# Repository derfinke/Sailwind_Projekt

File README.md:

# Projektarbeit: Sailwind Steuerung
 \
Firmware/Schaltplan für die Steuerung des Sailwind 4.0 Projekts.\
[ Für weitere Informationen](https://www.sailwind-power.eu/)

## Geteilte Dokumente
[Bauteile Tabelle](https://drive.google.com/drive/folders/1qaNF0T8h1C8PEslQvWO4vngNG08Ppogr?usp=share_link)

## Roadmap
- [x] Erstellung des Schaltplans
- [ ] Erstellung des PCB Designs
	- [x] Auswahl der Bauteile
- [ ] Erstellung der Firmware
	- [x] Definieren der genutzen Ports
	- [ ] Definition des Ethernet Protokoll
	- [ ] Siehe [open issues](https://github.com/derfinke/Sailwind_Projekt/issues)

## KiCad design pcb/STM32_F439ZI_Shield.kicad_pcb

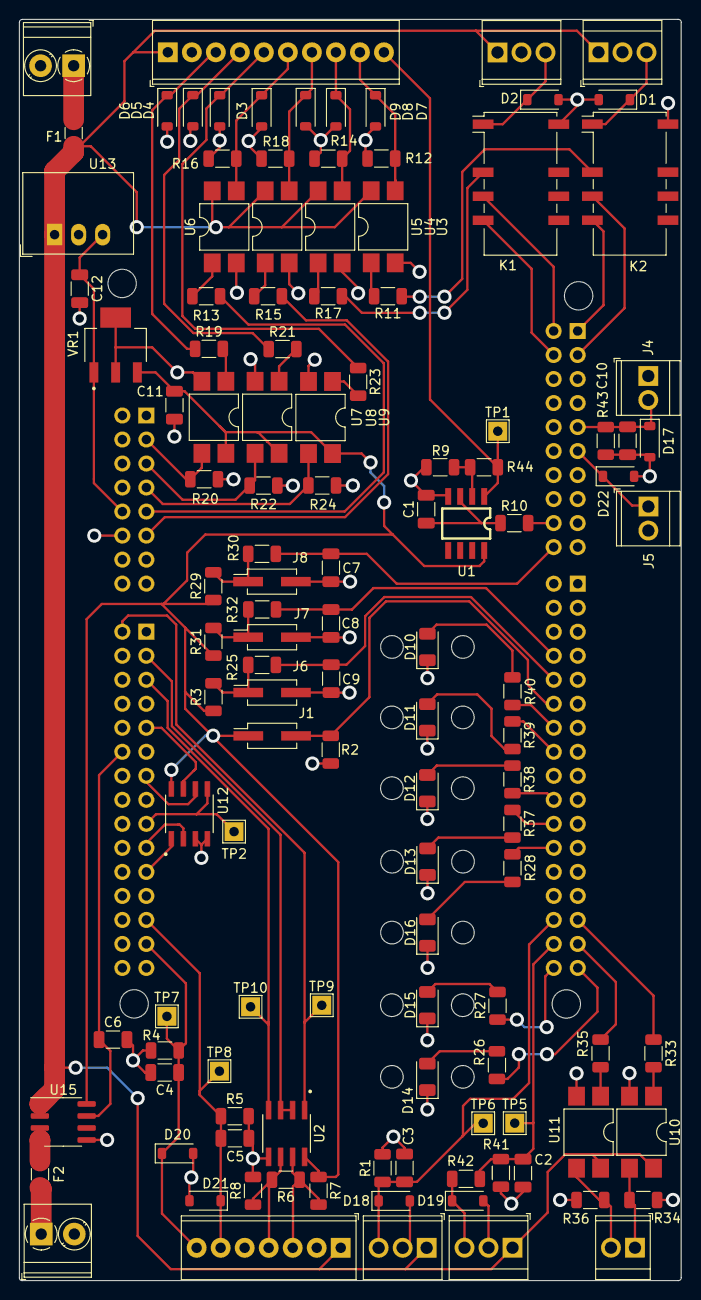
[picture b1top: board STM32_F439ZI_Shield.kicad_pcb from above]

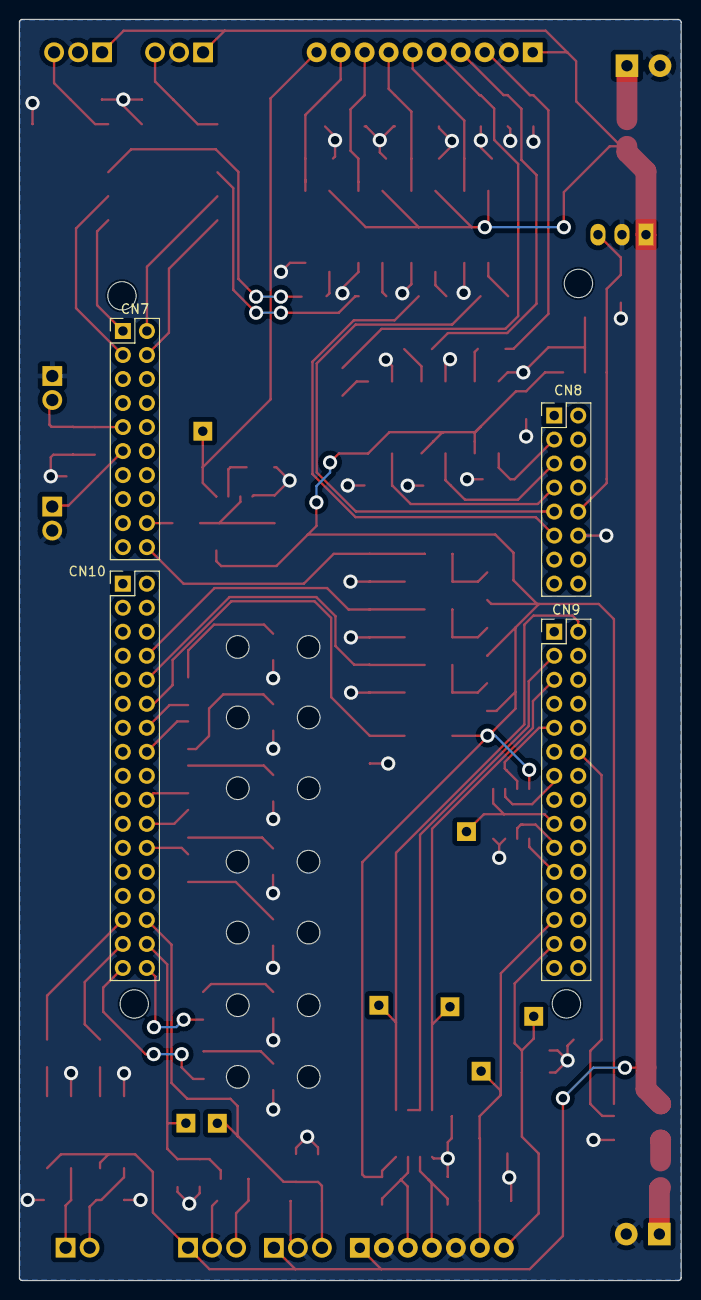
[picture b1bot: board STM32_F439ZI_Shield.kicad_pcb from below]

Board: 2 copper layers, 70.0 x 133.4 mm, 124 parts (4 on the bottom side), 83 nets.

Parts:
Abstandssensor1: Conn_01x03_Pin; TerminalBlock_TE_282834-3_1x03_P2.54mm_Horizontal
Anenometer1: Conn_01x07_Pin; TerminalBlock_TE_282834-7_1x07_P2.54mm_Horizontal
C1: 22u; C_1206_3216Metric
C2, C3, C4, C5, C6, C10: 22n; C_1206_3216Metric
C7, C8, C9: 220n; C_1206_3216Metric
C11: 33uF; C_1206_3216Metric
C12: 0.47uF; C_1206_3216Metric
CN7: Conn_02x10_Odd_Even; PinHeader_2x10_P2.54mm_Vertical
CN8: Conn_02x08_Odd_Even; PinHeader_2x08_P2.54mm_Vertical
CN9: Conn_02x15_Odd_Even; PinHeader_2x15_P2.54mm_Vertical
CN10: Conn_02x17_Odd_Even; PinHeader_2x17_P2.54mm_Vertical
D1: SMBJ5359B-TP; D_SOD-123
D2, D3, D4, D5, D6, D7, D8, D9: SMPJ5359B-TP; D_SOD-123
D10, D11, D16: LED_Green; LED_1206_3216Metric
D12, D14, D15: LED_Gelb; LED_1206_3216Metric
D13: LED_Red; LED_1206_3216Metric
D17, D18, D19, D20, D21, D22: KDZVTR6.8B; D_SOD-123
Endschalter_Hinten1: Conn_01x03_Pin; TerminalBlock_TE_282834-3_1x03_P2.54mm_Horizontal
Endschalter_Vorne1: Conn_01x03_Pin; TerminalBlock_TE_282834-3_1x03_P2.54mm_Horizontal
F1, F2: Fuse; Fuse_1206_3216Metric
J1, J6, J7, J8: Conn_01x02_Pin; PinHeader_2x01_P2.54mm_Vertical_SMD
J3: Relais_Conn; TerminalBlock_TE_282834-2_1x02_P2.54mm_Horizontal
J4, J5: Conn_01x02_Pin; TerminalBlock_TE_282834-2_1x02_P2.54mm_Horizontal
K1, K2: G6S-2; Relay_DPDT_Omron_G6S-2F
Kraftmessung1: Conn_01x04_Pin; TerminalBlock_TE_282834-3_1x03_P2.54mm_Horizontal
Motor_Logik1: Conn_01x10_Pin; TerminalBlock_TE_1-282834-0_1x10_P2.54mm_Horizontal
Motor_Spannungsversorgung1: Conn_01x02_Pin; TerminalBlock_Phoenix_PT-1,5-2-3.5-H_1x02_P3.50mm_Horizontal
R1, R4, R5, R28, R39, R40, R43: 150; R_1206_3216Metric
R2, R3, R9, R29, R31: 10k; R_1206_3216Metric
R6, R26, R27, R38: 120; R_1206_3216Metric
R7, R8: 750; R_1206_3216Metric
R10: 240; R_1206_3216Metric
R11, R13, R15, R17, R33, R35: 700; R_1206_3216Metric
R12, R14, R16, R18, R34, R36: 11k; R_1206_3216Metric
R19, R21, R23: 2,2k; R_1206_3216Metric
R20, R22, R24: 6,8k; R_1206_3216Metric
R25, R30, R32: 36k; R_1206_3216Metric
R37: 110; R_1206_3216Metric
R41: 2300; R_1206_3216Metric
R42: 1000; R_1206_3216Metric
R44: 0; R_1206_3216Metric
Spannungsversorgung_1: Conn_01x02_Pin; TerminalBlock_Phoenix_PT-1,5-2-3.5-H_1x02_P3.50mm_Horizontal
TP1, TP2, TP5, TP6, TP7, TP8, TP9, TP10: TestPoint; TestPoint_THTPad_2.0x2.0mm_Drill1.0mm
U1: LM2904; SO08
U2: MAX3485; SOIC127P600X175-8N
U3, U4, U5, U6, U7, U8, U9, U10, U11: LTV-817S; SMDIP-4_W7.62mm
U12: FL25L16B; SOIC127P602X172-8N
U13: R-78E-5.0-1.0; Converter_DCDC_RECOM_R-78E-0.5_THT
U15: ACS724xLCTR-05AB; SOIC-8_3.9x4.9mm_P1.27mm
VR1: LM3940IMP-3.3/NOPB; VREG_LM3940IMP-3.3_NOPB

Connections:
+3.3V: C11.1, J1.1, R3.1, R7.1, R29.1, R31.1, U1.8 (V+), U2.8 (VCC), U7.4, U8.4, U9.4, U12.8 (VDD), U15.8 (VCC), VR1.3 (OUT)
+5V: C12.1, CN8.10, U13.3 (OUT), VR1.1 (IN)
+24V: Abstandssensor1.1, Anenometer1.1, Endschalter_Hinten1.1, Endschalter_Vorne1.1, F1.2, Kraftmessung1.1, Motor_Logik1.1, U3.4, U4.4, U5.4, U6.4, U10.4, U11.4, U13.1 (IN), U15.1 (IP+), U15.2 (IP+)
/Buttons_LEDS/MCU_Kalibrierung: C9.1, CN10.10, R25.2
/Buttons_LEDS/MCU_LED_Betrieb: CN10.16, R39.1
/Buttons_LEDS/MCU_LED_Kalibrierung: CN10.24, R28.1
/Buttons_LEDS/MCU_LED_Manuell: CN10.20, R38.1
/Buttons_LEDS/MCU_LED_PWR: CN10.14, R40.1
/Buttons_LEDS/MCU_LED_Rollen: CN10.34, R27.1
/Buttons_LEDS/MCU_LED_Stoerung: CN10.22, R37.1
/Buttons_LEDS/MCU_LED_Trimmen: CN10.33, R26.1
/Buttons_LEDS/MCU_Switch: CN10.12, J1.2, R2.2
/Buttons_LEDS/MCU_Vorfahren: C7.1, CN7.20, R30.2
/Buttons_LEDS/MCU_Zurueckfahren: C8.1, CN10.8, R32.2
/Enable: CN9.3, U2.2 (~RE), U2.3 (DE)
/Endschalter/Endschalter_Hinten: D2.1 (K), Endschalter_Hinten1.3, K1.1
/Endschalter/Endschalter_Vorne: D1.1 (K), Endschalter_Vorne1.3, K2.1
/Motor/Drehzahl_Analog_OUT: Motor_Logik1.10, R44.1, TP1.1, U1.1
/Motor/IN0_OUT: D7.1 (K), Motor_Logik1.9, R12.1, U3.3
/Motor/IN1_OUT: D8.1 (K), Motor_Logik1.8, R14.1, U4.3
/Motor/IN2_OUT: D9.1 (K), Motor_Logik1.7, R18.1, U5.3
/Motor/IN3_OUT: D3.1 (K), Motor_Logik1.6, R16.1, U6.3
/Motor/OUT1_IN: D6.1 (K), Motor_Logik1.3, R19.1
/Motor/OUT2_IN: D5.1 (K), Motor_Logik1.4, R21.1
/Motor/OUT3_IN: D4.1 (K), Motor_Logik1.5, R23.1
/Motor/Stromsensor_MCU: C6.1, CN9.12, U15.7 (VIOUT)
/Optokoppler/Ext_Relais1_MCU: CN10.29, R33.1
/Optokoppler/Ext_Relais1_OUT: J3.1, R34.1, U10.3
/Optokoppler/Ext_Relais2_MCU: CN10.31, R35.1
/Optokoppler/Ext_Relais2_OUT: J3.2, R36.1, U11.3
/Optokoppler/IN0_MCU_IN: K2.3, R11.1
/Optokoppler/IN1_MCU_IN: K1.3, R17.1
/Optokoppler/IN2_MCU_IN: CN8.11, R15.1
/Optokoppler/IN3_MCU_IN: CN8.9, R13.1
/Optokoppler/OUT1_MCU: CN8.3, R20.1, U7.3
/Optokoppler/OUT2_MCU: CN8.5, R22.1, U8.3
/Optokoppler/OUT3_MCU: CN8.7, R24.1, U9.3
/Rx: CN9.2, TP9.1, U2.1 (RO)
/STM32F439ZI/Abstandsmessung_MCU: Abstandssensor1.3, C3.1, CN10.30, D18.1 (K), R1.1, TP6.1
/STM32F439ZI/CS: CN9.21, U12.1 (~CS)
/STM32F439ZI/Drehzahl_Analog_OUT: CN7.18, R10.2
/STM32F439ZI/Endschalter_Hinten_MCU: CN7.4, K1.5
/STM32F439ZI/Endschalter_Vorne_MCU: CN7.1, K2.5
/STM32F439ZI/HOLD: CN9.9, U12.7 (~HOLD)
/STM32F439ZI/IN0_MCU: CN7.3, K2.4
/STM32F439ZI/IN1_MCU: CN7.2, K1.4
/STM32F439ZI/Kraftmessung_MCU: C2.1, CN10.32, R41.1, R42.1, TP5.1
/STM32F439ZI/MISO: CN9.17, TP2.1, U12.5 (SI)
/STM32F439ZI/MOSI: CN9.19, U12.2 (SO)
/STM32F439ZI/Opt_Analog_IN: CN7.11, D22.1 (K), J5.1
/STM32F439ZI/Opt_Temperaturmessung: C10.1, CN7.9, D17.1 (K), J4.2, R43.1
/STM32F439ZI/SCK: CN9.13, U12.6 (SCK)
/STM32F439ZI/Windgeschwindigkeit_MCU: Anenometer1.7, C4.1, CN9.27, D20.1 (K), R4.1, TP7.1
/STM32F439ZI/Windrichtung_MCU: Anenometer1.6, C5.1, CN9.25, D21.1 (K), R5.1, TP8.1
/Sensoren_Eingänge/RS485_RX_TX_NEG_1: Anenometer1.3, R6.1, R7.2, U2.7 (B)
/Sensoren_Eingänge/RS485_RX_TX_POS_1: Anenometer1.4, R6.2, R8.1, U2.6 (A)
/Tx: CN9.5, TP10.1, U2.4 (DI)
GND: Abstandssensor1.2, Anenometer1.2, Anenometer1.5, C1.2, C2.2, C3.2, C4.2, C5.2, C6.2, C7.2, C8.2, C9.2, C10.2, C11.2, C12.2, CN8.12, D1.2 (A), D2.2 (A), D3.2 (A), D4.2 (A), D5.2 (A), D6.2 (A), D7.2 (A), D8.2 (A), D9.2 (A), D10.1 (K), D11.1 (K), D12.1 (K), D13.1 (K), D14.1 (K), D15.1 (K), D16.1 (K), D17.2 (A), D18.2 (A), D19.2 (A), D20.2 (A), D21.2 (A), D22.2 (A), Endschalter_Hinten1.2, Endschalter_Vorne1.2, J4.1, J5.2, J6.2, J7.2, J8.2, K1.12, K2.12, Kraftmessung1.2, Motor_Logik1.2, Motor_Spannungsversorgung1.2, R1.2, R2.1, R4.2, R5.2, R8.2, R9.2, R12.2, R14.2, R16.2, R18.2, R20.2, R22.2, R24.2, R34.2, R36.2, R42.2, R43.2, Spannungsversorgung_1.2, U1.4 (V-), U2.5 (GND), U3.2, U4.2, U5.2, U6.2, U7.2, U8.2, U9.2, U10.2, U11.2, U12.3 (~WP), U12.4 (GND), U13.2 (GND), U15.5 (GND), VR1.2 (GND_2), VR1.4 (GND_4)
unnamed: D10.2 (A), R40.2
unnamed: D11.2 (A), R39.2
unnamed: D12.2 (A), R38.2
unnamed: D13.2 (A), R37.2
unnamed: D14.2 (A), R26.2
unnamed: D15.2 (A), R27.2
unnamed: D16.2 (A), R28.2
unnamed: D19.1 (K), Kraftmessung1.3, R41.2
unnamed: F2.2, U15.3 (IP-), U15.4 (IP-)
unnamed: J6.1, R3.2, R25.1
unnamed: J7.1, R31.2, R32.1
unnamed: J8.1, R29.2, R30.1
unnamed: F2.1, Motor_Spannungsversorgung1.1
unnamed: R11.2, U3.1
unnamed: R13.2, U6.1
unnamed: R15.2, U5.1
unnamed: R17.2, U4.1
unnamed: R19.2, U7.1
unnamed: R21.2, U8.1
unnamed: R23.2, U9.1
unnamed: R33.2, U10.1
unnamed: R35.2, U11.1
unnamed: F1.1, Spannungsversorgung_1.1
unnamed: C1.1, R10.1, U1.3 (+)
unnamed: R9.1, R44.2, U1.2 (-)

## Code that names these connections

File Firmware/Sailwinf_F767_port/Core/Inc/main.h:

/* USER CODE BEGIN Header */
/**
  ******************************************************************************
  * @file           : main.h
  * @brief          : Header for main.c file.
  *                   This file contains the common defines of the application.
  ******************************************************************************
  * @attention
  *
  * Copyright (c) 2023 STMicroelectronics.
  * All rights reserved.
  *
  * This software is licensed under terms that can be found in the LICENSE file
  * in the root directory of this software component.
  * If no LICENSE file comes with this software, it is provided AS-IS.
  *
  ******************************************************************************
  */
/* USER CODE END Header */

/* Define to prevent recursive inclusion -------------------------------------*/
#ifndef __MAIN_H
#define __MAIN_H

#ifdef __cplusplus
extern "C" {
#endif

/* Includes ------------------------------------------------------------------*/
#include "stm32f7xx_hal.h"

/* Private includes ----------------------------------------------------------*/
/* USER CODE BEGIN Includes */

/* USER CODE END Includes */

/* Exported types ------------------------------------------------------------*/
/* USER CODE BEGIN ET */

/* USER CODE END ET */

/* Exported constants --------------------------------------------------------*/
/* USER CODE BEGIN EC */

/* USER CODE END EC */

/* Exported macro ------------------------------------------------------------*/
/* USER CODE BEGIN EM */

/* USER CODE END EM */

/* Exported functions prototypes ---------------------------------------------*/
void Error_Handler(void);

/* USER CODE BEGIN EFP */

/* USER CODE END EFP */

/* Private defines -----------------------------------------------------------*/
#define SPI4_CS_Pin GPIO_PIN_3
#define SPI4_CS_GPIO_Port GPIOE
#define USER_Btn_Pin GPIO_PIN_13
#define USER_Btn_GPIO_Port GPIOC
#define Switch_Betriebsmodus_Pin GPIO_PIN_4
#define Switch_Betriebsmodus_GPIO_Port GPIOF
#define Windrichtungmessung_Pin GPIO_PIN_7
#define Windrichtungmessung_GPIO_Port GPIOF
#define Windgeschwindigkeitmessung_Pin GPIO_PIN_9
#define Windgeschwindigkeitmessung_GPIO_Port GPIOF
#define Strommessung_Pin GPIO_PIN_10
#define Strommessung_GPIO_Port GPIOF
#define MCO_Pin GPIO_PIN_0
#define MCO_GPIO_Port GPIOH
#define RMII_MDC_Pin GPIO_PIN_1
#define RMII_MDC_GPIO_Port GPIOC
#define Kalibrierung_Pin GPIO_PIN_2
#define Kalibrierung_GPIO_Port GPIOC
#define Abstandsmessung_Pin GPIO_PIN_0
#define Abstandsmessung_GPIO_Port GPIOA
#define RMII_REF_CLK_Pin GPIO_PIN_1
#define RMII_REF_CLK_GPIO_Port GPIOA
#define RMII_MDIO_Pin GPIO_PIN_2
#define RMII_MDIO_GPIO_Port GPIOA
#define Windsensor_Rx_Pin GPIO_PIN_3
#define Windsensor_Rx_GPIO_Port GPIOA
#define Drehzahl_DAC_OUT_Pin GPIO_PIN_4
#define Drehzahl_DAC_OUT_GPIO_Port GPIOA
#define Analog_IN_Optional_Pin GPIO_PIN_6
#define Analog_IN_Optional_GPIO_Port GPIOA
#define RMII_CRS_DV_Pin GPIO_PIN_7
#define RMII_CRS_DV_GPIO_Port GPIOA
#define RMII_RXD0_Pin GPIO_PIN_4
#define RMII_RXD0_GPIO_Port GPIOC
#define RMII_RXD1_Pin GPIO_PIN_5
#define RMII_RXD1_GPIO_Port GPIOC
#define Kraftmessung_Pin GPIO_PIN_0
#define Kraftmessung_GPIO_Port GPIOB
#define Button_Zurueck_Pin GPIO_PIN_1
#define Button_Zurueck_GPIO_Port GPIOB
#define LED_Automatik_Pin GPIO_PIN_2
#define LED_Automatik_GPIO_Port GPIOB
#define Betriebsmodus_2_Nur_Prototyp_Pin GPIO_PIN_12
#define Betriebsmodus_2_Nur_Prototyp_GPIO_Port GPIOF
#define Betriebsmodus_Prototyp_Pin GPIO_PIN_15
#define Betriebsmodus_Prototyp_GPIO_Port GPIOF
#define Ext_Relais_1_Pin GPIO_PIN_15
#define Ext_Relais_1_GPIO_Port GPIOE
#define Ext_Relais_2_Pin GPIO_PIN_10
#define Ext_Relais_2_GPIO_Port GPIOB
#define LED_Trimmen_Pin GPIO_PIN_11
#define LED_Trimmen_GPIO_Port GPIOB
#define RMII_TXD1_Pin GPIO_PIN_13
#define RMII_TXD1_GPIO_Port GPIOB
#define Endschalter_Hinten_Pin GPIO_PIN_15
#define Endschalter_Hinten_GPIO_Port GPIOB
#define STLK_RX_Pin GPIO_PIN_8
#define STLK_RX_GPIO_Port GPIOD
#define STLK_TX_Pin GPIO_PIN_9
#define STLK_TX_GPIO_Port GPIOD
#define LED_Kalibrieren_Speichern_Pin GPIO_PIN_11
#define LED_Kalibrieren_Speichern_GPIO_Port GPIOD
#define LED_Stoerung_Pin GPIO_PIN_12
#define LED_Stoerung_GPIO_Port GPIOD
#define LED_Manuell_Pin GPIO_PIN_13
#define LED_Manuell_GPIO_Port GPIOD
#define IN_1_Pin GPIO_PIN_6
#define IN_1_GPIO_Port GPIOC
#define OUT_1_Pin GPIO_PIN_9
#define OUT_1_GPIO_Port GPIOC
#define OUT_2_Pin GPIO_PIN_10
#define OUT_2_GPIO_Port GPIOC
#define OUT_3_Pin GPIO_PIN_11
#define OUT_3_GPIO_Port GPIOC
#define IN_3_Pin GPIO_PIN_12
#define IN_3_GPIO_Port GPIOC
#define IN_2_Pin GPIO_PIN_2
#define IN_2_GPIO_Port GPIOD
#define HOLD_Pin GPIO_PIN_3
#define HOLD_GPIO_Port GPIOD
#define Windsensor_Tx_Pin GPIO_PIN_5
#define Windsensor_Tx_GPIO_Port GPIOD
#define Windsensor_EN_Pin GPIO_PIN_6
#define Windsensor_EN_GPIO_Port GPIOD
#define RMII_TX_EN_Pin GPIO_PIN_11
#define RMII_TX_EN_GPIO_Port GPIOG
#define RMII_TXD0_Pin GPIO_PIN_13
#define RMII_TXD0_GPIO_Port GPIOG
#define SWO_Pin GPIO_PIN_3
#define SWO_GPIO_Port GPIOB
#define Button_Vorfahren_Pin GPIO_PIN_4
#define Button_Vorfahren_GPIO_Port GPIOB
#define LED_PWR_Pin GPIO_PIN_6
#define LED_PWR_GPIO_Port GPIOB
#define Endschalter_Vorne_Pin GPIO_PIN_8
#define Endschalter_Vorne_GPIO_Port GPIOB
#define IN_0_Pin GPIO_PIN_9
#define IN_0_GPIO_Port GPIOB
#define LED_Rollen_Pin GPIO_PIN_0
#define LED_Rollen_GPIO_Port GPIOE

/* USER CODE BEGIN Private defines */

/* USER CODE END Private defines */

#ifdef __cplusplus
}
#endif

#endif /* __MAIN_H */

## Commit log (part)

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2023-03-23 Update README.md
    drive ordner mit stückliste und komponentendoc verlinkt
2023-03-27 added pcb design for STM32Shield
2023-03-27 added Subsheets vor different component types
2023-03-30 Updated PCB
2023-03-30 add dc/dc converter
2023-04-06 Refactored readme and added Docs + Firmware Directory
2023-04-06 fixed syntax
2023-04-06 Fixed Image Position
2023-04-06 Updated footprints
2023-04-06 added CubeIDE Project
2023-04-07 added/named necessary Pins
2023-04-07 Updated Roadmap
2023-04-13 added struct for analog sensors and function to read adc signal at respective channels
2023-04-13 fixed compile errors
2023-04-17 added methods to control dac and structs for the motor unit
2023-04-24 added function to measure motor rpm
2023-04-25 finished PCB Design V1.0
2023-05-03 added button_API with eventHandler and made private functions static
2023-05-03 added LED_API and renamed pointer with "ptr" ending
2023-05-03 added voltage regulator updated pinout
2023-05-04 added some new pins
2023-05-05 added calibration functionality and readme.txt for first test
2023-05-06 Revert "added some new pins"
    This reverts commit 4980527cb6c4fccf87e8775d8e5e0138ca49edcc.
2023-05-06 adjusted previous Code to new Pin Layout
2023-05-25 added accidentally removed htim10
2023-05-25 updated and verified motor_set_function() -> swapped motor_function_links/-rechtslauf
2023-05-25 changed type of analog sensor / actuator value to float
2023-05-26 updated and verified button_eventhandler() renamed IO functions and added digital state_change functions
2023-06-02 renamed private functions, reduced motor.calibration members, converted all division operands to float to increase precision and implemented calibrate_set_center function
2023-06-04 completed LED bar init function
2023-06-04 renamed hal pointer with "_ptr" ending, changed rpm measurement
2023-06-06 use motor_moving_state to control manual motor moving
2023-06-17 write description for each function
2023-06-18 added linear_guide_api and out-sourced calibration & endschalter functions from motor_API
2023-06-19 added FRAM init and FRAM read status register
2023-06-19 added IO_digitalPin Init function and adjusted GPIOx channels
2023-06-20 ported project to work on stm32f767zi
2023-06-20 improved calibration process and reduced level of nesting in some functions
2023-06-22 completed function documentation
2023-06-22 simplified calibration state machine
2023-06-23 added state diagram for calibration process
2023-06-24 merged FRAM and made Test functions
2023-07-13 added limitation to analog actuator object
2023-07-25 added testprotocol for windows
2023-07-25 added Docs/Kommunikation_mit_controllino.txt
2023-07-25 fixed Uart receive
2023-07-26 move all custom source files to Sailwind folder
2023-07-26 added init functions for OUT1 and AIN
2023-07-27 reduced redundant includes and added test_uart_poll function
2023-07-27 added more test cases to testprotocol
2023-07-30 enabled tim3 global interrupt
2023-07-31 added documentation folder and added test descriptions
2023-07-31 renamed functions, updated Localization state machine, changed motor Ins design
2023-07-31 added DISTANCE_PER_PULSE parameter for Localization Module
2023-08-01 added UART Module
2023-08-01 added LED test function
2023-08-01 added Endswitch Test
2023-08-01 changed Manual_Control design
2023-08-01 added Test_LED and Test_endswitch to Test_Documentation
2023-08-01 added button Test
2023-08-02 added update_sail_adjustment_mode function
2023-08-02 added Test Button to Document
2023-08-02 added functions for Localization struct (de-)serialization
2023-08-02 added function_call_hierarchy_test.pdf
2023-08-02 changed Endswitch test in function_call_hierarchy_test.pdf
2023-08-03 added FRAM test
2023-08-03 added more Tests to function_call_hierarchy_test.pdf
2023-08-06 simplified FRAM test
2023-08-07 added comments
2023-08-07 Added Jenkinsfile
2023-08-07 updated jenkinsfile
2023-08-07 added doxygen config
2023-08-07 removed arg
2023-08-07 added shell commands
2023-08-07 added Doxygen
2023-08-07 updated doxygen config
2023-08-07 renamed output directory
2023-08-08 added publishing to pipeline
2023-08-08 updated directory for doxygen publish
2023-08-08 added cppcheck config and added cppcheck stage to Jenkinsfile
2023-08-08 set multiline string
2023-08-08 fixed spelling
2023-08-08 removed output dir
2023-08-08 added cppcheck publishing
2023-08-08 added issue publishing
2023-08-08 fixed publishing
2023-08-08 simplified recordissues command
2023-08-08 trying to fix cppcheck
2023-08-08 added workaround
2023-08-08 updated suppressions
2023-08-08 fixed syntax and included Sailwind correctly
2023-08-09 added doxygen header
2023-08-09 tried to fix doxygen input
2023-08-09 reverted Extract all
2023-08-09 disabled graphwiz
2023-08-09 reenabled extarct all
2023-08-09 fixed wrong doxygen file shwoing up in interface
2023-08-13 Fixed FRAM.c
2023-08-13 replaced depricated function call
2023-08-13 fixed archiving path
2023-08-13 archive complete doxygen output
2023-08-13 added subdir to path
2023-08-13 added wildcard
2023-08-13 added shell command
2023-08-13 test syntax
2023-08-13 added update ton env variable
2023-08-13 activated shell output
2023-08-13 print output
2023-08-13 terminated string
2023-08-13 edited shell command
2023-08-13 fixed upload dir
2023-08-13 added print
2023-08-13 updated path again
2023-08-13 testing path
2023-08-13 test scripted section
2023-08-13 added char trimming
2023-08-14 corrected comment
2023-08-14 removed includes
2023-08-14 Fixed absolute paths
2023-08-14 fixed output dir
2023-08-14 set pins to correct level reduced clock speed
2023-08-14 added missing changes
2023-08-15 Added ID to Testspezifikationen
2023-08-15 added Distance Sensor module and added code formatting file
2023-08-16 fixed mm calculation and added doxygen comments
2023-08-16 fixed equation in doxygen
2023-08-17 Added ADC averaging
2023-08-21 changed IO analog functions
2023-08-22 added better adc avg
2023-08-22 updated values for dimension and amp
2023-08-26 modified settings
2023-08-26 changed function arguments
2023-08-26 removed part of adc initialization
2023-08-26 added WSWD module
2023-08-27 updated sensor types
2023-08-27 corrected procedure for getting current sensor values
2023-08-27 added wind direction sensor
2023-08-27 added protection for input and improved command construction
2023-08-27 added function to send commad with a parameter
2023-09-05 fixed rs485
2023-09-05 fixed current sensor accuracy
2023-09-06 fixed WSWD
2023-09-06 tried to fix approaching center
2023-09-06 test
2023-09-13 enabled lwip and generated first html page with fsdata
2023-09-16 added all changes
2023-09-16 added Request_Handler Module
2023-09-16 fixed firmware status
2023-09-17 enabled webserver updated lwip config for tcp
2023-09-17 added reading of current state to linear_guide_init
2023-09-17 added poll for trigger status of localization
2023-09-17 removed eth_init
2023-09-17 reincluded httpd.h
2023-09-17 removed request handler
2023-09-17 added tcp_server
2023-09-17 added request handler
2023-09-18 fixed html files and fsdata
2023-09-18 clean up & deleted rpm measurement features
2023-09-19 added localization reset feature
2023-09-19 added speed ramp
2023-09-19 cleanup includes and defines
2023-09-19 added REST Protokoll document
2023-09-19 added REST handling
2023-09-21 reset rpm_setpoint to 0 before activating speed ramp
2023-09-21 accelerated speed ramp and fixed final speed limitation
2023-09-21 added REST HTTP and JSON handling
2023-09-22 added "set_desired_pos" and "update_movement" function
2023-09-22 added get_roll_pitch_percentage function
2023-09-22 separated linearguide updates from pulse interrupt
2023-09-22 added additional html pages
2023-09-23 add ssi handler
2023-09-23 added doxygen comments
2023-09-23 adjusted html files for cgi
2023-09-23 added FRAM_write_enable to FRAM_write
2023-09-23 added error handling while saving position
2023-09-25 tested and fixed current changes
2023-09-25 changed button move forward with backwards
2023-09-25 added cgi and updated html pages
2023-09-25 added correct actions for cgi
2023-09-26 removed sconfig settings of adc / dac channels
2023-09-26 added doxygen comments for all public functions in Linear_Guide.h
2023-09-26 enabled global interrupt
2023-09-26 set correct error flag. motor now stops if different direction is chosen. sail pos is now displayed
2023-09-26 safe localization only after motor stop
2023-09-27 update inits of linear_guide and added distance sensor member
2023-09-27 added distance fault check and absolute localization when front Endswitch is detected
2023-09-27 added fault check status return value
2023-09-27 added current fault handling
2023-09-27 restored sconfig in dac init and removed sconfig declarations in adc inits
2023-09-27 switched led pins again
2023-09-28 added Memory mapping.h and replaced all normal FRAM addresses
2023-09-28 updated set_start_pos function to last merge
2023-09-28 fixed compile errors from merge
2023-09-28 changed error handling and added Endswitch handling in automatic mode
2023-09-28 added IP address swap through web interface
2023-09-29 removed speed in mm/s functions and added dac value conversion for rpm setting
2023-09-29 added negative speed ramp and immediate stop
2023-09-29 removed set desired roll / trim percentage test
2023-09-29 added function manual_move
2023-09-30 corrected errors and added instant stopping while moving through webserver
2023-09-30 fixed error
2023-10-01 added debugging of NMEA message
2023-10-01 fixed valid telegram
2023-10-01 added function for setting a max speed and a max allowed distance error
2023-10-01 added possibility to set distance fault and rpm during operation
2023-10-01 added saving of the newly set delta and max rpm
2023-10-02 added bug fixes
2023-10-02 added functions to queue new desired positions, if they're not on the current way
2023-10-02 changed switch operating mode function to toggle mode on each button edge
2023-10-02 REST: simplified sail adjustment json to +/- percentage (pitch / roll)
2023-10-04 applied +/- percentage change to webserver and Rest interface
2023-10-04 fixed set center from cgi handler
2023-10-04 replaced all occurrences of trim with pitch
2023-10-06 added blink timer interrupt and implemented setting / resetting of of ip address
2023-10-13 fixed IP Adress allocation
2023-10-13 save lwip.c
2023-10-14 added switching between dhcp and static IP at runtime
2023-10-14 fixed webserver display off pitch roll percentage
2023-10-16 fixed saving of Localization data -> motor moves again
2024-02-04 Added Documentation template
2024-02-04 Added more topics
2024-02-05 Rewrote Intro to chapter
2024-02-05 Added descriptions for some sensors
2024-02-06 Added Tables for Inputs and Outputs
2024-02-06 added one more subchapter
2024-02-10 Added more subtopics to section Hardware
2024-02-12 Added Descriptions and added goals
2024-02-13 Newest additions
2024-02-13 Added picture of Button and LED Layout and added usage desritpion
2024-02-14 Added pictures for PCB and general System
2024-02-15 Added better Introduction and presentation of goals
2024-02-15 removed unnecessary files
2024-02-15 added Software/IO Module sub chapter
2024-02-15 Added gitignore
2024-02-16 updated .gitignore
2024-02-16 ignore all .aux files
2024-02-16 Added pictures
2024-02-17 added Software->Steuerung der Linearführung->Umsetzung einer Rollung/Trimmung sub sub chapter
2024-02-17 Added Problem description
2024-02-17 Added Messungen
2024-02-18 added Optimierung der Bewegungsabläufe sub sub chapter
2024-02-18 Added Picture PCB inside the case
2024-02-18 added Fehlerbehandlung sub sub chapter
2024-02-19 added Einleitung chapter
2024-02-19 added Grundlagen der Segeleinstellung chapter
2024-02-19 Finished HArdware section
2024-02-20 added REST chapter and page brakes before all main sections
2024-02-20 Added Software sections
2024-02-20 added Zusammenfassung chapter
2024-02-20 added sources
2024-02-20 final touches
2024-02-21 fixed spelling in hardware chapter
2024-02-21 Finishing touches
2024-02-21 Added Signature to PDF
